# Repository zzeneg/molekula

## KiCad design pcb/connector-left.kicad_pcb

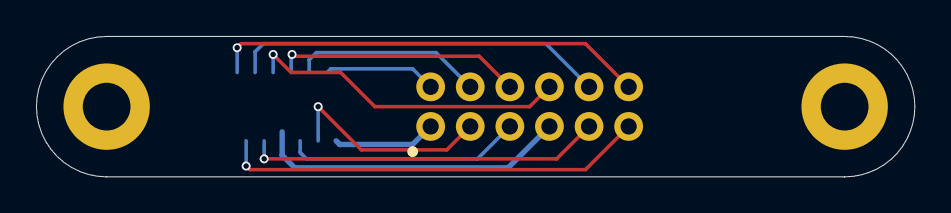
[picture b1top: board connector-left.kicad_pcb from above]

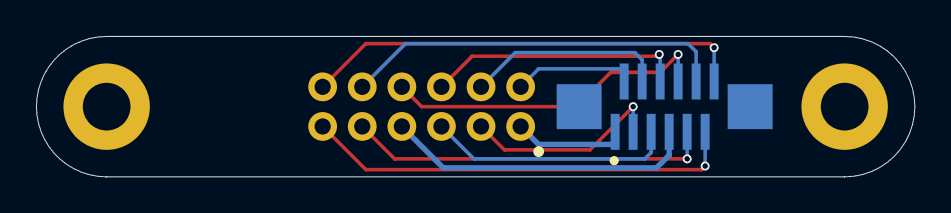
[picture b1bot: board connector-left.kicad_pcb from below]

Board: 2 copper layers, 48.8 x 7.8 mm, 4 parts (4 on the bottom side), 12 nets.

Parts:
H1, H2: MountingHole; Hole_M2-solder-nut-2.5
J8: C262499; Connector_FFC-12pin-0.5mm-vertical
J10: Conn_01x12_Socket; Connector_Magnetic-12pin

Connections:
BAT-conn1: J8.1, J10.1
GND: J8.7, J10.7
col0-conn1: J8.6, J10.6
col1-conn1: J8.5, J10.5
col2-conn1: J8.4, J10.4
col3-conn1: J8.3, J10.3
col4-conn1: J8.2, J10.2
free-conn1: J8.12, J10.12
row0-conn1: J8.11, J10.11
row1-conn1: J8.10, J10.10
row2-conn1: J8.9, J10.9
row3-conn1: J8.8, J10.8

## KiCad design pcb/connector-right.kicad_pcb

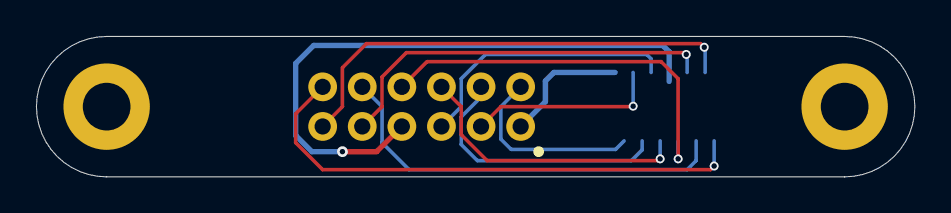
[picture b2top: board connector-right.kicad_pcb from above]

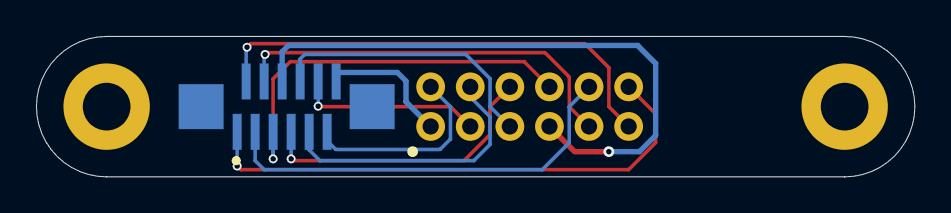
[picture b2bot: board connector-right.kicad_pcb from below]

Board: 2 copper layers, 48.8 x 7.8 mm, 4 parts (3 on the bottom side), 12 nets.

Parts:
H3, H4: MountingHole; Hole_M2-solder-nut-2.5
J9: C262499; Connector_FFC-12pin-0.5mm-vertical
J11: Conn_01x12_Socket; Connector_Magnetic-12pin

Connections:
BAT-conn2: J9.12, J11.1
GND: J9.6, J11.7
col0-conn2: J9.7, J11.6
col1-conn2: J9.8, J11.5
col2-conn2: J9.9, J11.4
col3-conn2: J9.10, J11.3
col4-conn2: J9.11, J11.2
free-conn2: J9.1, J11.12
row0-conn2: J9.2, J11.11
row1-conn2: J9.3, J11.10
row2-conn2: J9.4, J11.9
row3-conn2: J9.5, J11.8

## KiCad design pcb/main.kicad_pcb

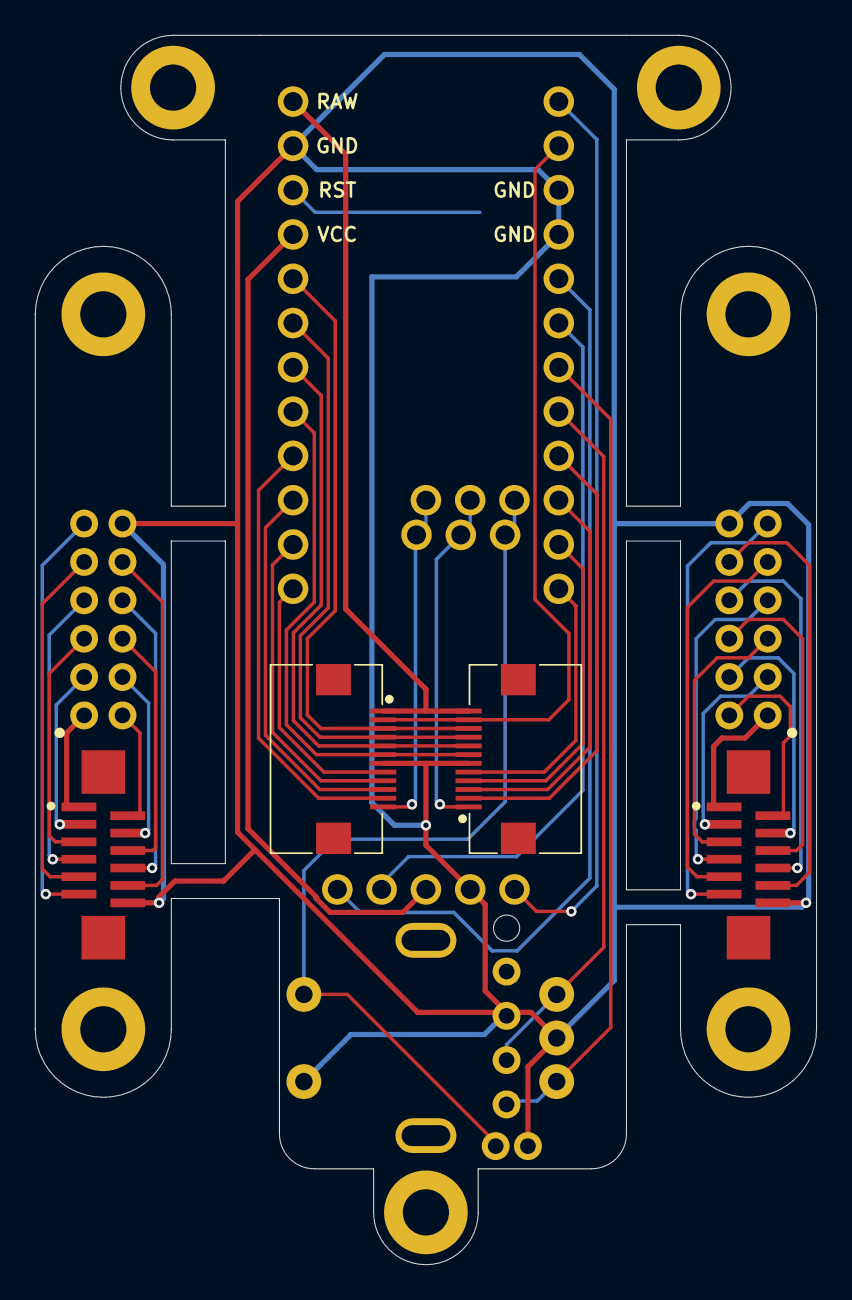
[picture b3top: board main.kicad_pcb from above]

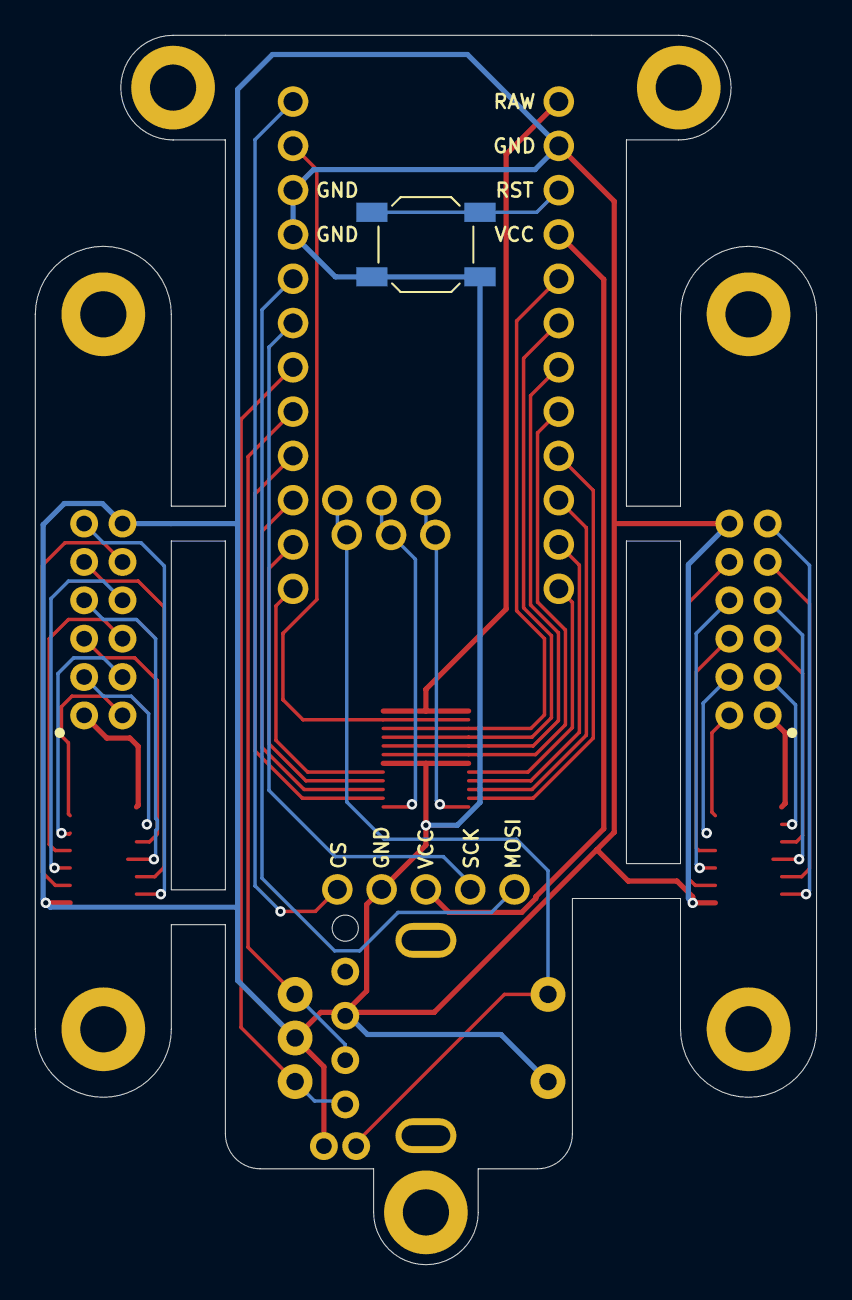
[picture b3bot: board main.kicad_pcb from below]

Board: 2 copper layers, 44.8 x 70.5 mm, 18 parts (3 on the bottom side), 9 nets.

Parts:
H1, H2, H3, H4, H5, H6, H7: MountingHole; Hole_M2-solder-nut-2.5
J1: N!N; MCU_nice-nano
J2, J3: Conn_01x12_Socket; Connector_FFC-12pin-0.5mm-horizontal
J6: Display_nice-view
J8, J9: Conn_01x12_Socket; Connector_FFC-12pin-0.5mm-vertical
J10, J11: Conn_01x12_Socket; Connector_Magnetic-12pin
SW37: SW_Push; Button_SW_SPST_SKQG_WithoutStem
SW38: RotaryEncoder_Switch; RotaryEncoder_EC11
U1: RollerEncoder_EVQWGD001; RotaryEncoder_EVQWGD001

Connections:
+3.3V: J1.21 (3V3), J6.3 (VCC)
CS: J1.1 (006), J6.5 (CS)
GND: J1.3 (GND), J1.4 (GND), J1.23 (GND), J2.7, J3.6, J6.4 (GND), J8.12, J9.12, J10.12, J11.12, SW37.2, SW38.C, SW38.S2, U1.C, U1.S1
MOSI: J1.5 (017), J6.1 (MOSI)
OFF: J1.31 (101), SW38.S1, U1.S2
RST: J1.22 (RST), SW37.1
SCK: J1.6 (020), J6.2 (SCK)
encA: J1.7 (022), SW38.A, U1.A
encB: J1.8 (024), SW38.B, U1.B

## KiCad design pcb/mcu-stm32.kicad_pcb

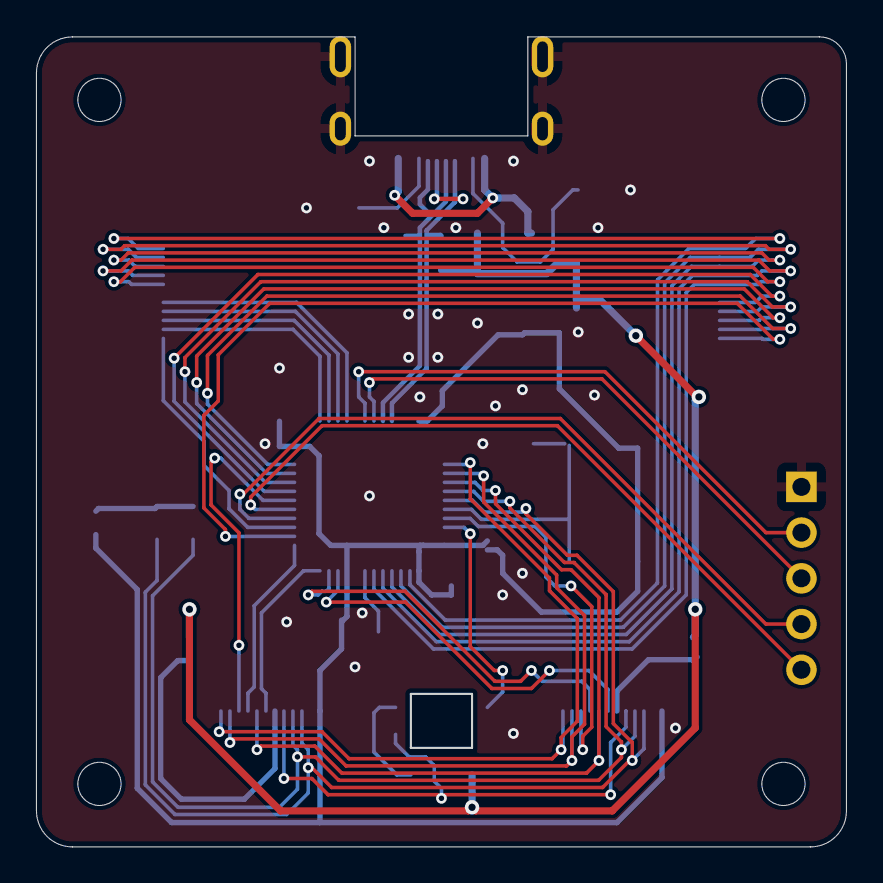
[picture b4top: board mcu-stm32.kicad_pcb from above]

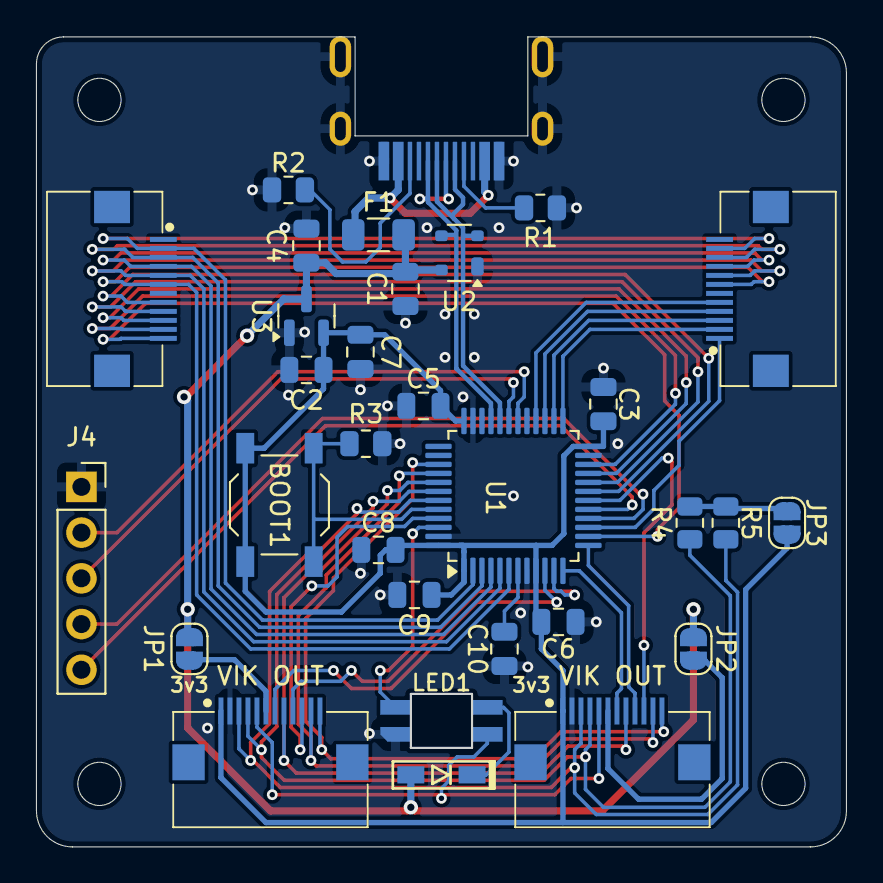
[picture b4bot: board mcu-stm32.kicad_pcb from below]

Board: 2 copper layers, 45.0 x 45.0 mm, 35 parts (31 on the bottom side), 46 nets.

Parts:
BOOT1: SW_SPST; SW_SPST_TL3342
C1, C3, C5, C6, C8, C9, C10: 100nF; C_0805_2012Metric
C2: 10uF; C_0805_2012Metric
C4, C7: 1uF; C_0805_2012Metric
D1: D; Diode_1N4148-SOD123
F1: 1A; Fuse_1206_3216Metric
H1, H2, H3, H4: MountingHole; Hole_M2
J1: USB_C_Receptacle_USB2.0; Connector_USB-C-mid-mount-ali
J2, J3: Conn_01x12_Socket; Connector_FFC-12pin-0.5mm-horizontal
J4: Conn_01x05_Pin; PinSocket_1x05_P2.54mm_Vertical
JP1, JP2: 5V; SolderJumper-2_P1.3mm_Open_RoundedPad1.0x1.5mm
JP3: VCC; SolderJumper-2_P1.3mm_Open_RoundedPad1.0x1.5mm
LED1: YS-SK6812MINI-E; LED_SK6812-MINI-E
R1, R2: 5.1k; R_0805_2012Metric
R3: 10k; R_0805_2012Metric
R4, R5: 4.7k; R_0805_2012Metric
U1: STM32F072CBT6; LQFP-48_7x7mm_P0.5mm
U2: PRTR5V0U2X; SOT-143
U3: XC6206PxxxMR-Regulator_Linear; SOT-23
VIK_K1, VIK_K2: Connector_VIK-keyboard; Connector_VIK-horizontal-keyboard

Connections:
+3V3: BOOT1.1 (A), C2.1, C3.1, C5.1, C6.1, C7.1, C8.1, C9.1, JP3.2 (B), U1.1 (VBAT), U1.9 (VDDA), U1.24 (VDD), U1.36 (VDDIO2), U1.48 (VDD), U3.2 (VO), VIK_K1.1 (3V3), VIK_K2.1 (3V3)
+5V: C1.1, C4.1, D1.2 (A), F1.2, JP1.1 (A), JP2.1 (A), U2.4 (VCC), U3.3 (VI)
BOOT0: BOOT1.2 (B), R3.1, U1.44 (BOOT0)
D+: J1.A6 (D+), J1.B6 (D+), U1.33 (PA12), U2.3 (I/O2)
D-: J1.A7 (D-), J1.B7 (D-), U1.32 (PA11), U2.2 (I/O1)
ENCA: J4.2, U1.30 (PA9)
ENCB: J4.3, U1.31 (PA10)
ENCS1: J4.4, U1.16 (PA6)
ENCS2: J4.5, U1.17 (PA7)
GND: C1.2, C2.2, C3.2, C4.2, C5.2, C6.2, C7.2, C8.2, C9.2, C10.2, J1.A1 (GND), J1.A12 (GND), J1.B1 (GND), J1.B12 (GND), J1.S1 (SHIELD), J4.1, LED1.3 (VSS), R1.1, R2.2, R3.2, U1.8 (VSSA), U1.23 (VSS), U1.35 (VSS), U1.47 (VSS), U2.1 (GND), U3.1 (GND), VIK_K1.2 (GND), VIK_K2.2 (GND)
I2C_3V3: JP3.1 (A), R4.1, R5.1
LED: LED1.4 (DIN), U1.46 (PB9)
LED_OUT: LED1.2 (DOUT), VIK_K1.5 (RGB_LED_OUT), VIK_K2.5 (RGB_LED_OUT)
NRST: C10.1, U1.7 (NRST)
unnamed: D1.1 (K), LED1.1 (VDD)
unnamed: J1.A5 (CC1), R1.2
unnamed: J1.B5 (CC2), R2.1
SCL: R4.2, U1.42 (PB6), VIK_K1.4 (SCL), VIK_K2.4 (SCL)
SDA: R5.2, U1.43 (PB7), VIK_K1.3 (SDA), VIK_K2.3 (SDA)
SPI_CLK: U1.39 (PB3), VIK_K1.12 (SCLK), VIK_K2.12 (SCLK)
SPI_MISO: U1.40 (PB4), VIK_K1.11 (MISO), VIK_K2.11 (MISO)
SPI_MOSI: U1.41 (PB5), VIK_K1.8 (MOSI), VIK_K2.8 (MOSI)
VBUS: F1.1, J1.A4 (VBUS), J1.A9 (VBUS), J1.B4 (VBUS), J1.B9 (VBUS)
VIK1_5V: JP1.2 (B), VIK_K1.6 (5V)
VIK1_CS: U1.45 (PB8), VIK_K1.10 (SPI_CS)
VIK1_GPIO1: U1.10 (PA0), VIK_K1.7 (GPIO_AD1)
VIK1_GPIO2: U1.11 (PA1), VIK_K1.9 (GPIO_AD2)
VIK2_5V: JP2.2 (B), VIK_K2.6 (5V)
VIK2_CS: U1.18 (PB0), VIK_K2.10 (SPI_CS)
VIK2_GPIO1: U1.12 (PA2), VIK_K2.7 (GPIO_AD1)
VIK2_GPIO2: U1.13 (PA3), VIK_K2.9 (GPIO_AD2)
col0-mcu: J2.6, J3.7, U1.6 (PF1)
col1-mcu: J2.5, J3.8, U1.5 (PF0)
col2-mcu: J2.4, J3.9, U1.4 (PC15)
col3-mcu: J2.3, J3.10, U1.3 (PC14)
col4-mcu: J2.2, J3.11, U1.2 (PC13)
free1-mcu: J2.12, U1.14 (PA4)
free2-mcu: J3.1, U1.15 (PA5)
row0-mcu: J2.11, U1.22 (PB11)
row1-mcu: J2.10, U1.21 (PB10)
row2-mcu: J2.9, U1.20 (PB2)
row3-mcu: J2.8, U1.19 (PB1)
row4-mcu: J3.5, U1.28 (PB15)
row5-mcu: J3.4, U1.27 (PB14)
row6-mcu: J3.3, U1.26 (PB13)
row7-mcu: J3.2, U1.25 (PB12)

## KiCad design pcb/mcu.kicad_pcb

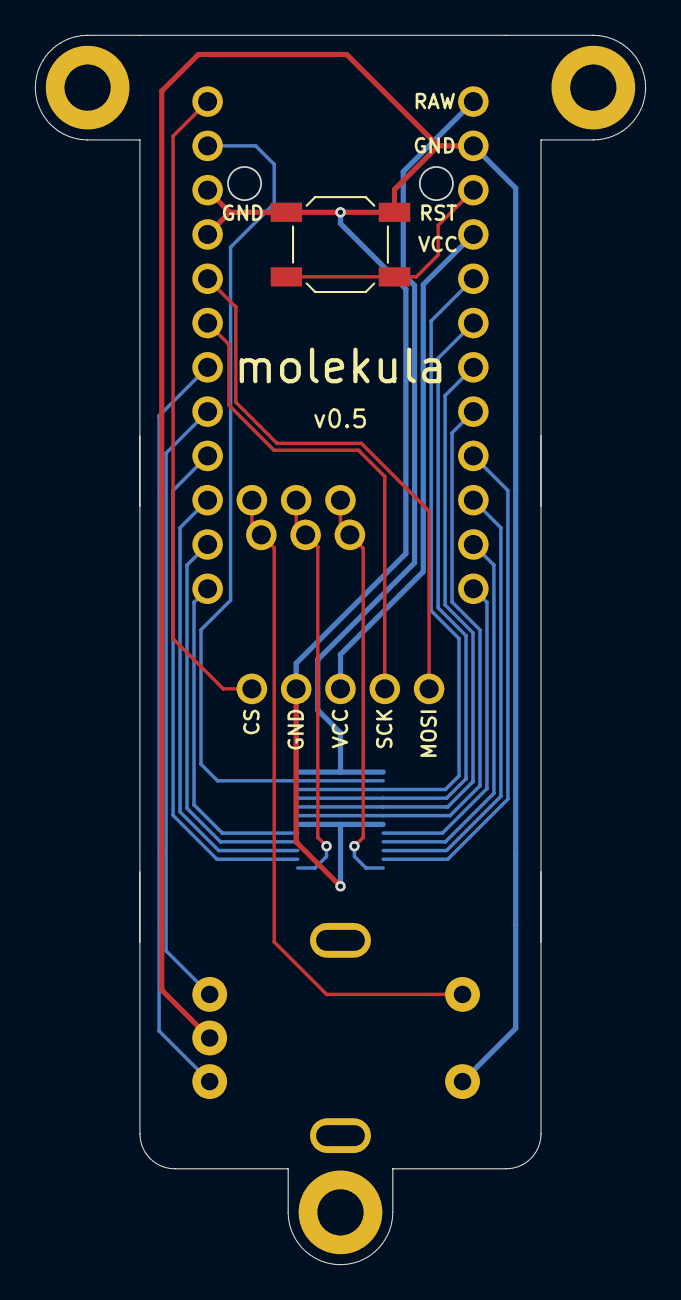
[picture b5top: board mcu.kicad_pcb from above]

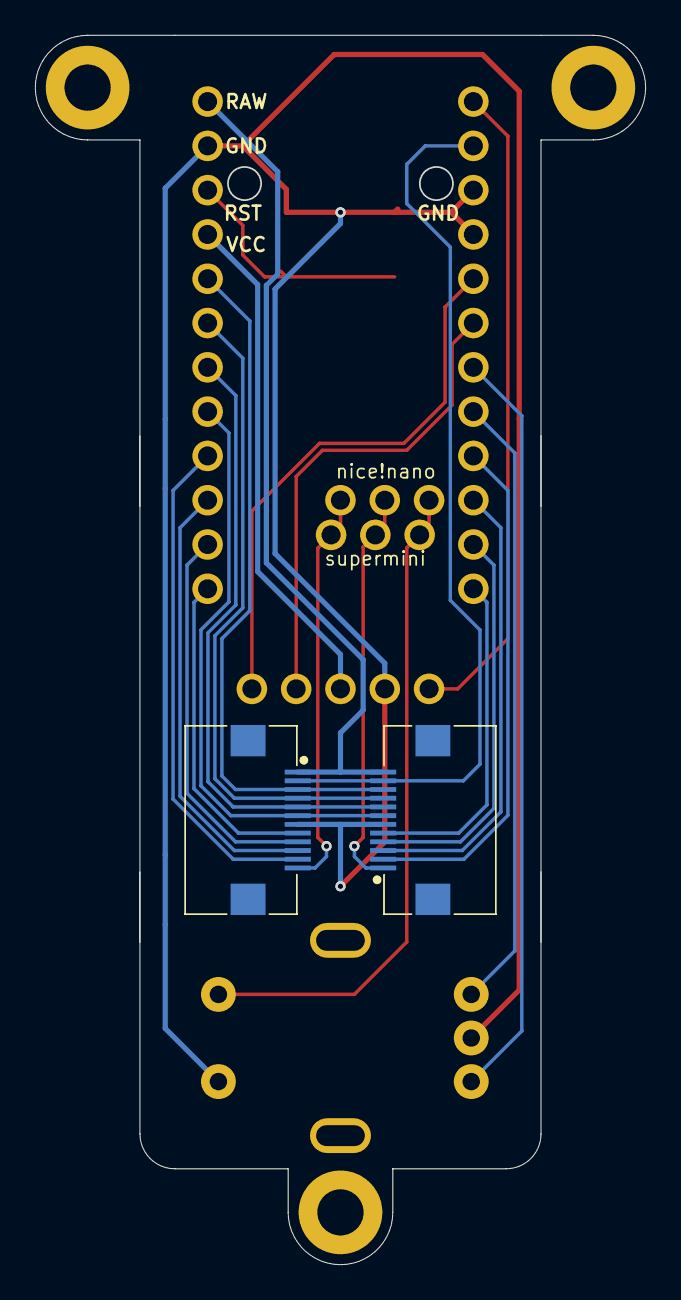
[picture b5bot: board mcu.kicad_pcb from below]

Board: 2 copper layers, 35.0 x 70.5 mm, 9 parts (7 on the bottom side), 25 nets.

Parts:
H5, H6, H7: MountingHole; Hole_M2-solder-nut-2.5
J1: N!N; MCU_nice-nano
J2, J3: C479750; Connector_FFC-12pin-0.5mm-horizontal
J6: Display_nice-view
SW37: SW_Push; Button_SW_SPST_SKQG_WithoutStem
SW38: RotaryEncoder_Switch; RotaryEncoder_EC11

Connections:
+3.3V: J1.21 (3V3), J6.3 (VCC)
BAT-mcu: J1.24 (BAT), J2.1, J3.12
CS: J1.1 (006), J6.5 (CS)
GND: J1.3 (GND), J1.4 (GND), J1.23 (GND), J2.7, J3.6, J6.4 (GND), SW37.1, SW38.C, SW38.S2
MOSI: J1.5 (017), J6.1 (MOSI)
OFF: J1.31 (101), SW38.S1
RST: J1.22 (RST), SW37.2
SCK: J1.6 (020), J6.2 (SCK)
col0-mcu: J1.17 (115), J2.6, J3.7
col1-mcu: J1.18 (002), J2.5, J3.8
col2-mcu: J1.19 (029), J2.4, J3.9
col3-mcu: J1.20 (031), J2.3, J3.10
col4-mcu: J1.2 (008), J2.2, J3.11
encA: J1.7 (022), SW38.A
encB: J1.8 (024), SW38.B
free1-mcu: J1.33 (107), J2.12
free2-mcu: J1.32 (102), J3.1
row0-mcu: J1.16 (113), J2.11
row1-mcu: J1.15 (111), J2.10
row2-mcu: J1.14 (010), J2.9
row3-mcu: J1.13 (009), J2.8
row4-mcu: J1.12 (106), J3.5
row5-mcu: J1.11 (104), J3.4
row6-mcu: J1.10 (011), J3.3
row7-mcu: J1.9 (100), J3.2

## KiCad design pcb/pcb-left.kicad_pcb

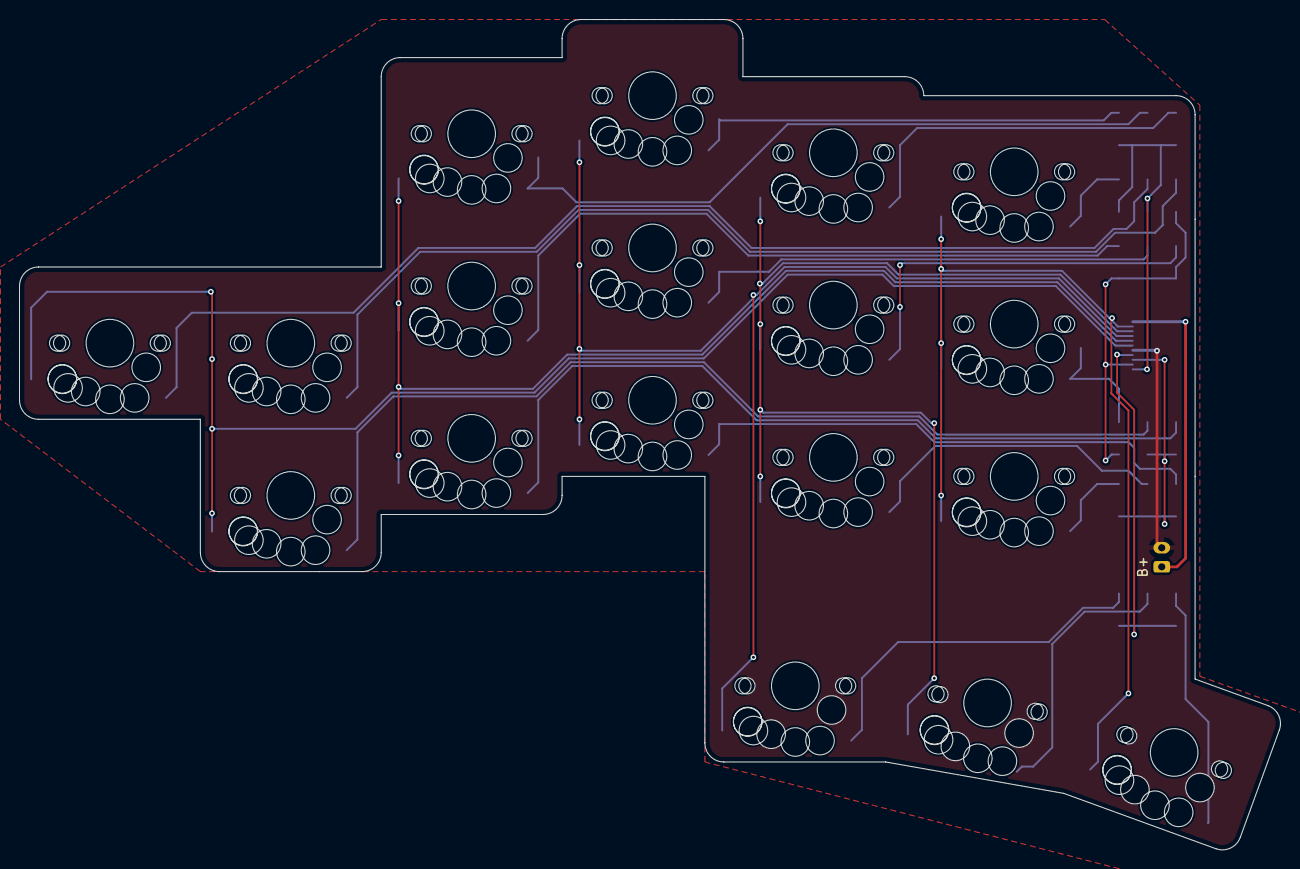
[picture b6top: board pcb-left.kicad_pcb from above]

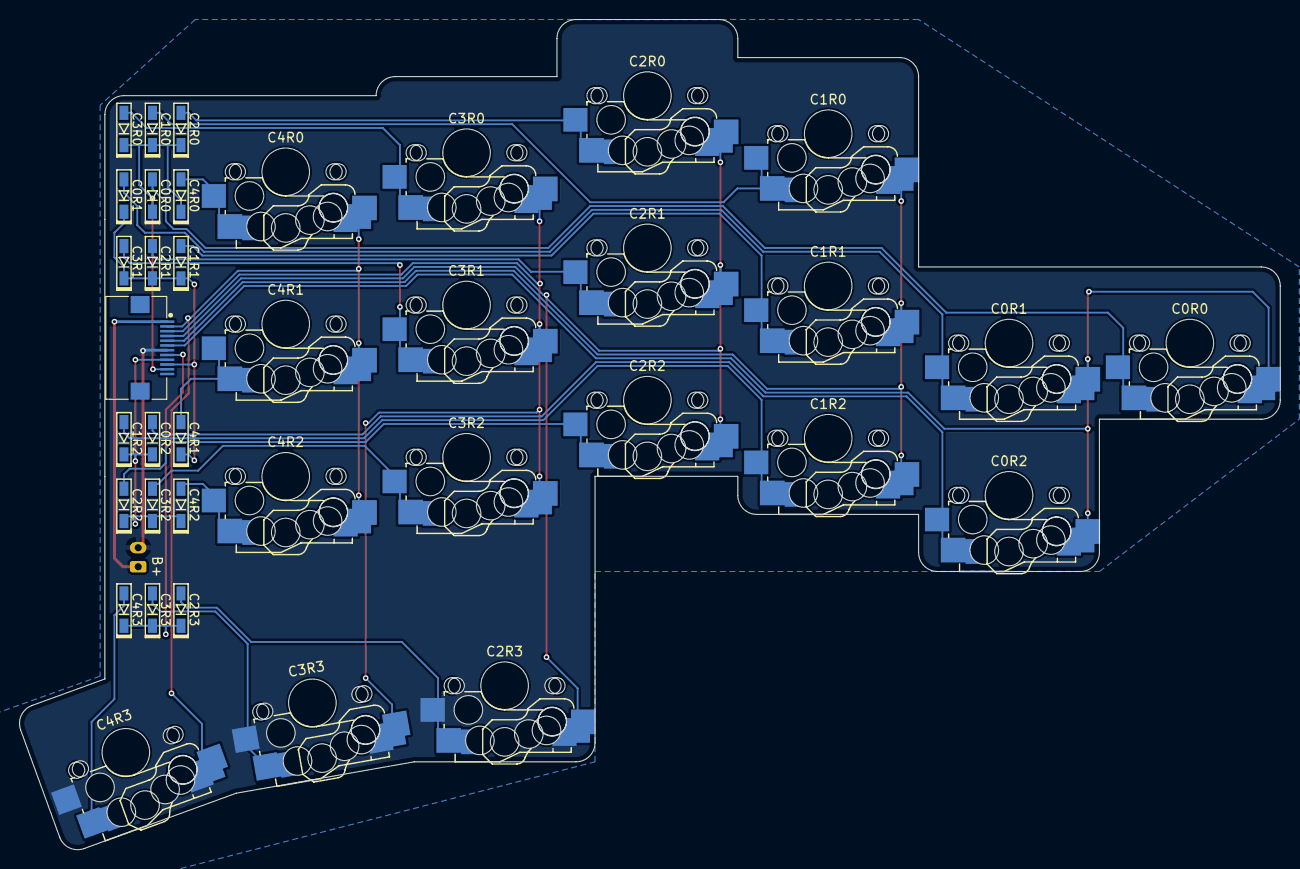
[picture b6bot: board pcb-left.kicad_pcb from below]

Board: 2 copper layers, 132.5 x 87.2 mm, 38 parts (19 on the bottom side), 29 nets.

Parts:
D1, D2, D3, D4, D5, D6, D7, D8, D9, D10, D11, D12, D13, D14, D15, D16, D17, D18: C81598; Diode_1N4148-SOD123
J4: C479750; Connector_FFC-12pin-0.5mm-horizontal
J7: Conn_01x02_Socket; Connector_JST-1x02-2.00mm
SW1, SW2, SW3, SW4, SW5, SW6, SW7, SW8, SW9, SW10, SW11, SW12, SW13, SW14, SW15, SW16, SW17, SW18: Switch; Switch_MXKSChoc-miny-hotswap-ks-3d

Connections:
BAT-left: J4.1, J7.1
GND: J4.7, J7.2
unnamed: D1.2 (A), SW1.1
unnamed: D2.2 (A), SW2.1
unnamed: D3.2 (A), SW3.1
unnamed: D4.2 (A), SW4.1
unnamed: D5.2 (A), SW5.1
unnamed: D6.2 (A), SW6.1
unnamed: D7.2 (A), SW7.1
unnamed: D8.2 (A), SW8.1
unnamed: D9.2 (A), SW9.1
unnamed: D10.2 (A), SW10.1
unnamed: D11.2 (A), SW11.1
unnamed: D12.2 (A), SW12.1
unnamed: D13.2 (A), SW13.1
unnamed: D14.2 (A), SW14.1
unnamed: D15.2 (A), SW15.1
unnamed: D16.2 (A), SW16.1
unnamed: D17.2 (A), SW17.1
unnamed: D18.2 (A), SW18.1
col0: J4.6, SW1.2, SW6.2, SW11.2
col1: J4.5, SW2.2, SW7.2, SW12.2
col2: J4.4, SW3.2, SW8.2, SW13.2, SW16.2
col3: J4.3, SW4.2, SW9.2, SW14.2, SW17.2
col4: J4.2, SW5.2, SW10.2, SW15.2, SW18.2
row0: D1.1 (K), D2.1 (K), D3.1 (K), D4.1 (K), D5.1 (K), J4.11
row1: D6.1 (K), D7.1 (K), D8.1 (K), D9.1 (K), D10.1 (K), J4.10
row2: D11.1 (K), D12.1 (K), D13.1 (K), D14.1 (K), D15.1 (K), J4.9
row3: D16.1 (K), D17.1 (K), D18.1 (K), J4.8
